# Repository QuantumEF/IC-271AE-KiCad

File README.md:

# KiCad Schematics of the IC-271A/E VHF radio
Creating for my own reference and general documentation.

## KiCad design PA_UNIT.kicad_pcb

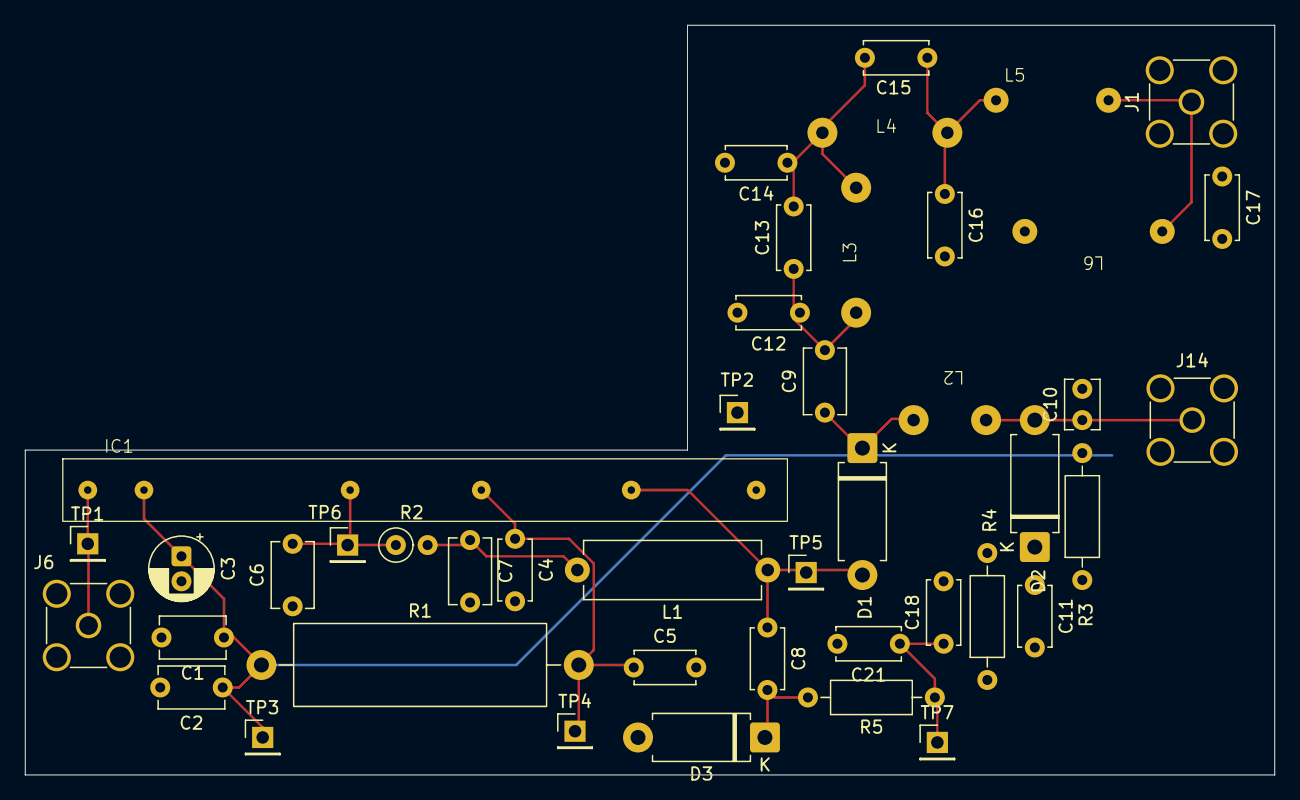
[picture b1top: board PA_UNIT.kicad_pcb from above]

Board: 2 copper layers, 100.0 x 60.0 mm, 44 parts (0 on the bottom side), 16 nets.

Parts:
C1, C6: Ceramic 220 pF 50V; C_Disc_D5.1mm_W3.2mm_P5.00mm
C2: Barrier Lay 0.1 16V; C_Disc_D5.1mm_W3.2mm_P5.00mm
C3: Electrolytic 22uF 16V; CP_Radial_D5.0mm_P2.00mm
C4: Barrier Lay 0.1 16V; C_Disc_D4.7mm_W2.5mm_P5.00mm
C5: Ceramic 220 pF 50V; C_Disc_D4.7mm_W2.5mm_P5.00mm
C7: Ceramic 0.0047 50V; C_Disc_D5.1mm_W3.2mm_P5.00mm
C8: Ceramic 0.5 pF 500V; C_Disc_D4.7mm_W2.5mm_P5.00mm
C9: Ceramic 0.001 500V; C_Disc_D5.1mm_W3.2mm_P5.00mm
C10: Ceramic 15 pF 50V; C_Disc_D3.8mm_W2.6mm_P2.50mm
C11: Ceramic 150pF 50V; C_Disc_D4.7mm_W2.5mm_P5.00mm
C12: Ceramic 39pF 500V; C_Disc_D5.0mm_W2.5mm_P5.00mm
C13: Ceramic 3pF 500V; C_Disc_D5.0mm_W2.5mm_P5.00mm
C14: Ceramic 33pF 500V; C_Disc_D4.7mm_W2.5mm_P5.00mm
C15: Ceramic 2pF 500V; C_Disc_D5.0mm_W2.5mm_P5.00mm
C16: Ceramic 33pF 500V; C_Disc_D5.0mm_W2.5mm_P5.00mm
C17: Ceramic 15pF 500V; C_Disc_D5.0mm_W2.5mm_P5.00mm
C18: Ceramic 0.0047 50V; C_Disc_D5.0mm_W2.5mm_P5.00mm
C21: Ceramic 220 pF 50V; C_Disc_D5.0mm_W2.5mm_P5.00mm
D1, D2: MI402; D_DO-15_P10.16mm_Horizontal
D3: 1SS97; D_DO-15_P10.16mm_Horizontal
IC1: SC-1020
J1: RF_Ant; SMA_Amphenol_901-144_Vertical
J6: TX_Input; SMA_Amphenol_901-144_Vertical
J14: RX_Output; SMA_Amphenol_901-144_Vertical
L1: Coil LW-10; L_Axial_L14.0mm_D4.5mm_P15.24mm_Horizontal_Fastron_LACC
L2: Coil LA-2; Inductor_6x8
L3: Coil LA-71; Inductor_6x12
L4: Coil LA-9; Inductor_6x10
L5: Coil LA-76; Inductor_L5
L6: Choke LW-19; Inductor_L6
R1: 0.15? 3W; R_Axial_Power_L20.0mm_W6.4mm_P25.40mm
R2: 220 ELR25; R_Axial_DIN0207_L6.3mm_D2.5mm_P2.54mm_Vertical
R3: 1.5k R25; R_Axial_DIN0207_L6.3mm_D2.5mm_P10.16mm_Horizontal
R4: 220 R25; R_Axial_DIN0207_L6.3mm_D2.5mm_P10.16mm_Horizontal
R5: 47k? R25; R_Axial_DIN0207_L6.3mm_D2.5mm_P10.16mm_Horizontal
TP1: TP-J6; PinHeader_1x01_P2.54mm_Vertical
TP2: TP-J7; PinHeader_1x01_P2.54mm_Vertical
TP3: TP-J8,J9; PinHeader_1x01_P2.54mm_Vertical
TP4: TP-J10; PinHeader_1x01_P2.54mm_Vertical
TP5: TP-J11; PinHeader_1x01_P2.54mm_Vertical
TP6: TP-J12; PinHeader_1x01_P2.54mm_Vertical
TP7: TP-J15; PinHeader_1x01_P2.54mm_Vertical

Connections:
+12V: C1.1, C2.1, C3.1, IC1.2 (VCC1), R1.1, R3.2, TP3.1
GND: C1.2, C2.2, C3.2, C4.2, C5.2, C6.1, C7.2, C10.2, C11.2, C12.2, C14.2, C16.2, C17.2, C18.2, C21.2, D3.2 (A), IC1.6 (GND), J1.2 (Ext), J6.2 (Ext), J14.2 (Ext), L6.2, R4.1, TP2.1
unnamed: C7.1, L1.2, R2.2
unnamed: C9.2, C12.1, C13.1, L3.1
unnamed: C13.2, C14.1, C15.1, L3.2, L4.1
unnamed: C15.2, C16.1, L4.2, L5.1
unnamed: C8.1, D1.2 (A), IC1.5, L1.1, TP5.1
unnamed: C9.1, D1.1 (K), L2.2
unnamed: C10.1, D2.2 (A), J14.1 (In), L2.1
unnamed: C11.1, D2.1 (K), R3.1, R4.2
unnamed: C8.2, D3.1 (K), R5.2
unnamed: IC1.1 (IN), J6.1 (In), TP1.1
unnamed: C6.2, IC1.3 (VBB), R2.1, TP6.1
unnamed: C4.1, C5.1, IC1.4 (VCC2), R1.2, TP4.1
unnamed: C17.1, J1.1 (In), L5.2, L6.1
unnamed: C18.1, C21.1, R5.1, TP7.1

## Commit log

2026-05-04 Notes and Minor Tweaks
2026-05-04 Renamed files for clarity
2026-05-04 Path change for the PA_UNIT footprints
2026-05-04 Tranmitter Notes from Service manual
2026-05-04 add readme
